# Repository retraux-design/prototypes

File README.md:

# Setup

## Git Large File Storage

Install [git-lfs](https://git-lfs.github.com/) to fetch datasheet PDFs and other
large files.

## KiCad Libraries

TODO

# KiCad Style Guide

TODO

## Schematics

## Naming

* Group decoupling caps with ICs (so U1 has cap C1, etc)
* Keep references contiguous for related parts (R10+R11, not R23+R14)
* Always prefer `~NET` to `nNET`/etc
* Always prefer `NET+`/`NET-` to `NET_P`/`NET_N`/etc

### Hierarchy

* Use hierarchical schematics for large functional blocks
* Always prefer hierarchical pins to global net names

### Passives

* Prefer resistor arrays on proto boards (smaller component count)
* Use `R_Small` and `C_Small` to keep schematic smaller
* Always use the `Capacitor_SMD_RD` and `Resistor_SMD_RD` footprints
* Prefer 0603 for NFF boards and 0402 for FF boards

### Connectors

#### I2C

* Follow the [SparkFun Qwiic](https://www.sparkfun.com/qwiic) standard
  * Right-angle connector: [JST SM04B-SRSS-TB](https://www.digikey.com/product-detail/en/jst-sales-america-inc/SM04B-SRSS-TB-LF-SN/455-1804-1-ND/926875)
  * Vertical connector: [JST BM04B-SRSS-TB](https://www.digikey.com/product-detail/en/jst-sales-america-inc/BM04B-SRSS-TB(LF)(SN)/455-1790-1-ND/926861)
  * Pin order:
    1. `GND` (black)
    2. `3V3` (red)
    3. `SDA` (blue)
    4. `SCL` (yellow)
* `~INT` can be exposed by a [2 pos 2.54mm header](https://www.digikey.com/product-detail/en/sullins-connector-solutions/GBC01DABN-M30/S2351E-01-ND/6605225)
  * Pin order:
    1. `~INT`
    2. `GND`

#### UART

* Use the same Qwiic connector as for I2C
  * Pin order:
    1. `GND` (black)
    2. `3V3` (red)
    3. `TX` (blue)
    4. `RX` (yellow)

#### USB

* Prefer [JAE DX07B024JJR1500](https://www.digikey.com/product-detail/en/jae-electronics/DX07B024JJ1R1500/670-2795-1-ND/5246071) mid-mount USB-C 3.1 connector
* TODO(benvanik): test [JAE DX07W024JA1R1000](https://www.digikey.com/product-detail/en/jae-electronics/DX07W024JA1R1000/670-3100-1-ND/9646472) for waterproof use

#### Board-to-Board

* Samtech Q Strip-series QSE/QTE
  * [QSE-020-01-F-D-A](https://www.digikey.com/product-detail/en/samtec-inc/QSE-020-01-F-D-A/SAM8955-ND/2664407) 40-pos receptacle
  * [QTE-020-01-F-D-A](https://www.digikey.com/product-detail/en/samtec-inc/QTE-020-01-F-D-A/SAM8846-ND/3079641) 40-pos header

## PCBs

### Units

* Prefer metric
* Larger components aligned to 0.5mm grid
* Smaller components/traces aligned to 0.25mm grid

### Silkscreen

* Use 1x1mm / 0.15mm font (smaller may be unreadable from JLCPCB)
* Align reference labels to footprint boundary when possible
* Hide reference labels for mounting holes and other misc footprints
* Prefer human-readable labels instead of references for major IO ports

### Physical Design

* Prefer M2 grounded mounting holes with vias (or M3 for larger boards)
* Use 90deg arcs with a 0.55mm radius for board corners
* Include several 0.5mm fiducials
* Avoid through-hole components where possible (prefer SMD pin headers/etc)
* Use 2.54mm pin headers for NFF boards (jumpers/etc)

### Layer Stackup

(from [Controlling Radiated EMI Through PCB Stack-up](https://www.eetimes.com/document.asp?doc_id=1214998))

#### 4 Layers

1. Signal
1. GND
1. Power
1. Signal

#### 6 Layers

1. Signal
1. GND
1. Signal
1. Power
1. GND
1. Signal

#### 8 Layers

1. Signal
1. GND
1. Signal
1. Power
1. GND
1. Signal
1. GND
1. Signal

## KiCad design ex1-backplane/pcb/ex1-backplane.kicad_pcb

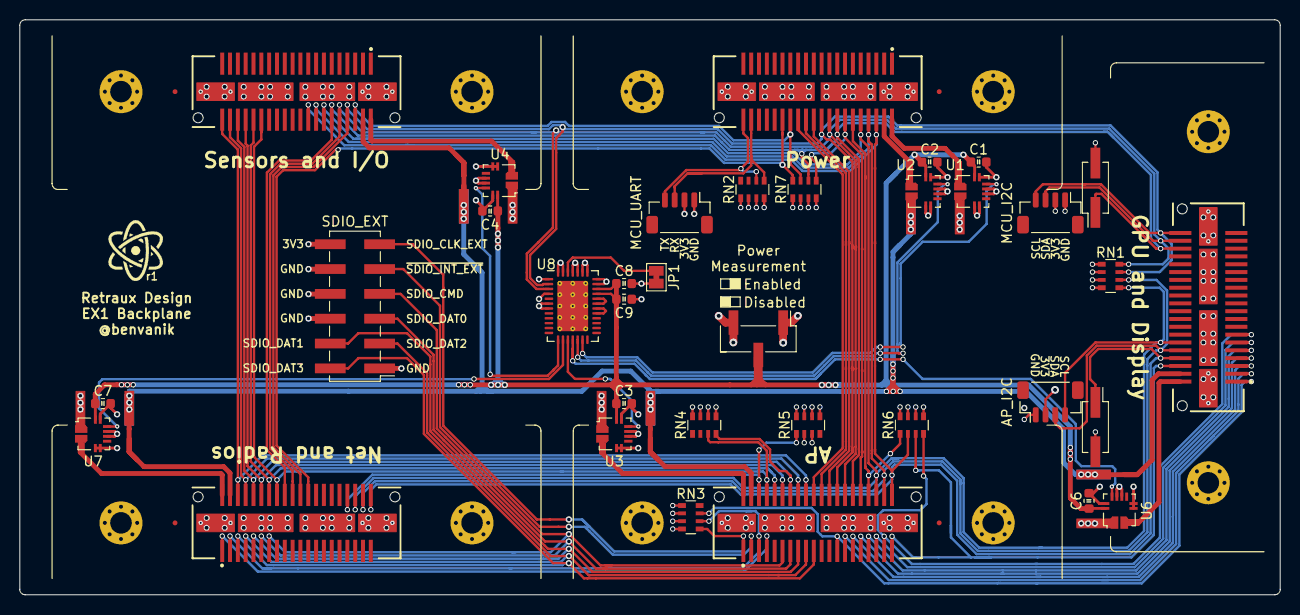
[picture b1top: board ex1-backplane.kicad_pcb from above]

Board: 4 copper layers, 128.9 x 58.8 mm, 45 parts (0 on the bottom side), 58 nets.

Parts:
C1, C2, C3, C4, C6, C7, C8: 0.1uF; C_0603_1608Metric
C9: 10uF; C_0603_1608Metric
H1, H2, H3, H4, H5, H6, H7, H8, H9, H10: MountingHole_Pad; MountingHole_2.2mm_M2_Pad_Via
J1: Power; Samtech_QSE-020-01-X-D-A
J2: AP; Samtech_QSE-020-01-X-D-A
J3: Sensors; Samtech_QSE-020-01-X-D-A
J4: GPU; Samtech_QSE-020-01-X-D-A
J5: Net; Samtech_QSE-020-01-X-D-A
J6: SDIO_EXT; PinHeader_2x06_P2.54mm_Vertical_SMD
J7: MCU_I2C_INT; PinHeader_2x01_P2.54mm_Vertical_SMD
J8: MCU_I2C; JST_SH_BM04B-SRSS-TB_1x04-1MP_P1.00mm_Vertical
J9: MCU_UART; JST_SH_BM04B-SRSS-TB_1x04-1MP_P1.00mm_Vertical
J10: AP_I2C_INT; PinHeader_2x01_P2.54mm_Vertical_SMD
J11: AP_I2C; JST_SH_BM04B-SRSS-TB_1x04-1MP_P1.00mm_Vertical
J12: Measurement EN; PinHeader_1x03_P2.54mm_Vertical_SMD_Pin1Left
JP1: CA0; SolderJumper-2_P1.3mm_Bridged_Pad1.0x1.5mm
RN1, RN2: 4K7; R_Array_Convex_4x0603
RN3, RN4, RN5, RN6, RN7: 50K; R_Array_Convex_4x0603
U1, U2, U3, U4, U6, U7: ACS70331EESATR; Allegro_QFN-12-10-1EP_3x3mm_P0.5mm
U8: Linear_Technology_LTC2497; QFN-38-1EP_5x7mm_P0.5mm_EP3.15x5.15mm_ThermalVias

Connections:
+3V3: J6.12, J8.2, J9.2, J11.2, J12.1, RN1.1, RN1.2, RN1.3, RN1.4, RN2.1, RN2.2, RN2.3, RN2.4, RN5.1, RN5.2, RN5.3, RN5.4, RN6.1, RN6.2, RN6.3, RN6.4, RN7.1, RN7.2, RN7.3, RN7.4, U1.2, U3.1, U4.1, U6.1, U7.1
+BATT: J2.4, J3.4, J4.4, J5.4, U2.2
/AP_I2C_SCL: J1.10, J2.36, J3.14, J4.12, J5.36, J11.4, RN1.5
/AP_I2C_SDA: J1.8, J2.38, J3.16, J4.10, J5.38, J11.3, RN1.6
/AP_I2S_IN_SCK: J2.8, J3.30, J5.16, RN4.7
/AP_I2S_IN_SD: J2.12, J3.34, J5.12
/AP_I2S_IN_WS: J2.10, J3.32, J5.14
/AP_I2S_OUT_SCK: J2.14, J3.36, J5.10, RN4.8
/AP_I2S_OUT_SD: J2.18, J3.40, J5.6
/AP_I2S_OUT_WS: J2.16, J3.38, J5.8
/AP_RAIL_3V3: J2.2, U3.2
/AP_SDIO_CLK_EXT: J2.1, J6.11, RN3.5
/AP_SDIO_CLK_GPU: J2.25, J4.1, RN3.7
/AP_SDIO_CLK_NET: J2.5, J5.3, RN3.6
/AP_SDIO_CMD: J2.11, J5.13, J6.7
/AP_SDIO_CMD_GPU: J2.27, J4.3
/AP_SDIO_DAT0: J2.13, J5.11, J6.5
/AP_SDIO_DAT0_GPU: J2.29, J4.5
/AP_SDIO_DAT1: J2.15, J5.9, J6.4
/AP_SDIO_DAT1_GPU: J2.31, J4.7
/AP_SDIO_DAT2: J2.17, J5.7, J6.3
/AP_SDIO_DAT2_GPU: J2.33, J4.9
/AP_SDIO_DAT3: J2.19, J5.5, J6.2
/AP_SDIO_DAT3_GPU: J2.35, J4.11
/GPU_RAIL_3V3: J4.2, U6.2
/INPUT_RAIL_3V3: J1.2, U1.1
/INPUT_RAIL_VBAT: J1.4, U2.1
/MCU_I2C_SCL: J1.20, J2.26, J3.8, J4.40, J5.22, J8.4, RN1.7, U8.2
/MCU_I2C_SDA: J1.18, J2.28, J3.10, J4.38, J5.20, J8.3, RN1.8, U8.3
/MCU_UART_RX: J1.40, J9.4, RN2.6
/MCU_UART_TX: J1.38, J9.3, RN2.5
/NET_RAIL_3V3: J5.2, U7.2
/Power Measurement/AP_RAIL_3V3_VI: U3.8, U8.15
/Power Measurement/CA0: JP1.2, U8.36
/Power Measurement/GPU_RAIL_3V3_VI: U6.8, U8.16
/Power Measurement/INPUT_RAIL_3V3_VI: U1.8, U8.18
/Power Measurement/INPUT_RAIL_VBAT_VI: U2.8, U8.17
/Power Measurement/NET_RAIL_3V3_VI: U7.8, U8.14
/Power Measurement/PWR_MEASURE_EN: C1.1, C2.1, C3.1, C4.1, C6.1, C7.1, C8.1, C9.1, J12.2, U1.10, U2.10, U3.10, U4.10, U6.10, U7.10, U8.28, U8.29
/Power Measurement/SENSOR_RAIL_3V3_VI: U4.8, U8.13
/SENSOR_RAIL_3V3: J3.2, U4.2
/USB_D+: J1.24, J2.22
/USB_D-: J1.22, J2.24
/USB_VBUS: J1.26, J2.20
/~AP_GPU_INT: J2.39, J4.6, RN6.7
/~AP_I2C_INT: J1.6, J2.40, J3.18, J4.8, J5.40, J10.1, RN6.6
/~AP_MCU_INT: J1.12, J2.34, RN6.5
/~AP_NET_INT: J2.6, J5.34, RN5.5
/~AP_SDIO_INT_EXT: J2.3, J6.9, RN5.6
/~AP_SDIO_INT_GPU: J2.37, J4.13, RN6.8
/~AP_SDIO_INT_NET: J2.7, J5.1, RN5.7
/~MCU_AP_INT: J1.14, J2.32, RN7.5
/~MCU_I2C_INT: J1.16, J2.30, J3.12, J4.36, J5.18, J7.1, RN7.6
/~MCU_NET_INT: J1.30, J5.24, RN7.8
/~MCU_SENSOR_INT: J1.28, J3.6, RN7.7
GND: C1.2, C2.2, C3.2, C4.2, C6.2, C7.2, C8.2, C9.2, H1.1, H2.1, H3.1, H4.1, H5.1, H6.1, H7.1, H8.1, H9.1, H10.1, J1.41, J1.42, J1.43, J1.44, J2.41, J2.42, J2.43, J2.44, J3.41, J3.42, J3.43, J3.44, J4.41, J4.42, J4.43, J4.44, J5.41, J5.42, J5.43, J5.44, J6.1, J6.6, J6.8, J6.10, J7.2, J8.1, J9.1, J10.2, J11.1, J12.3, JP1.1, RN3.1, RN3.2, RN3.3, RN3.4, RN4.1, RN4.2, RN4.3, RN4.4, U1.3, U1.4, U1.6, U1.7, U1.9, U2.3, U2.4, U2.6, U2.7, U2.9, U3.3, U3.4, U3.6, U3.7, U3.9, U4.3, U4.4, U4.6, U4.7, U4.9, U6.3, U6.4, U6.6, U6.7, U6.9, U7.3, U7.4, U7.6, U7.7, U7.9, U8.1, U8.4, U8.6, U8.7, U8.30, U8.31, U8.32, U8.33, U8.34, U8.35, U8.37, U8.38, U8.39
unnamed: U8.24, U8.25
unnamed: U8.26, U8.27

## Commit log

2019-06-28 EX1 Backplane prototype r1.
2019-06-28 Ignoring out/ dirs.
2019-06-28 Fixing backplane label overlap.
2019-06-28 Adding readme with KiCad style.
2019-06-29 Power and GPU modules skeletons.
2019-06-29 Removing unneeded cache lib.
